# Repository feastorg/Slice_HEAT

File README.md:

# DC heating Element Controller Slice

DC heating Element Controller Slice for BREAD.

## Introduction

Two-channel controller for resistive DC heating elements, with a
MAX31855K thermocouple input per channel. Each channel has a high-side
P-channel MOSFET (AOD4185) that is on only while the bus E-stop and the
Nano's enable are both high, and a low-side N-channel MOSFET (AOD4184A)
switched by the Nano's PWM. A B340A freewheel diode sits across each
output.

## Ratings

- Heater supply: 12 V only, on its own terminal block J6 (VHTR+ and
  VHTR- = PGND), not from the bus. Fit an external 8 A slow-blow fuse
  in the + lead.
- Up to 3.5 A per channel, 7 A for both together.
- Resistive heaters: up to 3.5 A per channel. An inductive load (solenoid,
  fan, pump) relies on the on-board freewheel diodes D3/D4 alone, and they
  are B340A parts rated 3 A average: keep inductive loads to 3 A per
  channel.
- PGND meets the logic ground at one point on the board (NT1).
- FET heat: the drain tabs of Q2-Q4 sit on 1.74-1.93 cm2 of 1 oz
  copper each (F.Cu and B.Cu, joined by thermal vias; Q1 4.95 cm2), less
  than the 1 in2 of 2 oz behind the datasheets' RθJA. At 3.5 A and
  100 % duty, with RDS(on) at TJ 125 C, the AOD4184A low side dissipates
  0.20 W and the AOD4185 high side 0.38 W, so TJ at 50 C ambient is at
  most about 70 C and 88 C. These are estimates: RθJA is assumed to be
  100 C/W, not measured. Bench check before relying on 3.5 A: run
  both channels at 3.5 A for 30 minutes with a thermocouple on each FET
  tab (Q1-Q4).

## Connections

Wires enter all four terminal blocks from the right-hand board edge;
each position is marked on the silkscreen.

| Terminal | Pin | Signal | Use |
|---|---|---|---|
| J4 | 2 / 1 | HTR1+ / HTR1- | heater 1 |
| J5 | 2 / 1 | HTR2+ / HTR2- | heater 2 |
| J6 | 2 / 1 | VHTR+ / VHTR- (PGND) | 12 V heater supply in |
| J3 | 5 / 6 | TC1+ / TC1- | type K thermocouple, channel 1 (U2) |
| J3 | 7 / 8 | TC2+ / TC2- | type K thermocouple, channel 2 (U3) |
| J3 | 1 / 2, 3 / 4 | TMSTR1 (TH1) / GND, TMSTR2 (TH2) / GND | thermistor inputs (R1/R2 pull-ups to +5V) |

J4-J6 are Phoenix Contact SPT 2,5/ 2-H-5,0 (1990973): 2-position
push-in, 5 mm pitch, 24 A, 0.2-4 mm2 rigid or 0.2-2.5 mm2 flexible
wire, 10 mm strip length. J3 is a Phoenix Contact PT 1,5/ 8-3,5-H
(8-position push-in, 3.5 mm pitch).

E-stop: the bus E_STOP line (J2.6) must be high for the heaters to run.
Unwired, a 1 M pull-down holds it low and the heaters stay off.
JP1 (BENCH, open by default) pulls the line high through R18 (10 k) for use off
the loaf; leave it open in a loaf.

## Warnings

- Thermocouples: use insulated (sheathed or ungrounded-junction) probes.
  A junction touching a live heater conductor puts up to 12 V on T+/T-,
  far past the MAX31855's absolute maximum of VCC + 0.3 V (3.6 V on its
  3.3 V supply), and can destroy it.
- Heater supply polarity: J6 pin 2 is + (VHTR+), pin 1 is - (VHTR-).
  Reversed, the TVS D2 and
  the MOSFET body diodes with the freewheel diodes conduct straight
  across the supply until the external fuse opens, and C7 (polarised)
  is reverse biased. There is no reverse-polarity protection on the
  board: check the polarity before connecting the supply.

## Pin map (Arduino Nano, A1)

| Nano pin | Signal | Function |
|---|---|---|
| D11 | PWM1 | heater 1 low-side gate |
| D10 | PWM2 | heater 2 low-side gate |
| D12 | HTR_EN | high = high-side switches may turn on |
| D2 | ESTOP_SNS | buffered E-stop, input (high = run) |
| D9 | CLK | MAX31855 clock (software SPI, 3.3 V shifted) |
| D7 | DATA | MAX31855 SO |
| D8 | SS1 | thermocouple 1 chip select |
| D6 | SS2 | thermocouple 2 chip select |
| D5 | LED | WS2812B status LED |
| A0 / A1 | TMSTR1 / TMSTR2 | thermistor inputs (unused by the sketch) |
| A4 / A5 | I2C | bus I2C (slice address 6) |

## Usage

> **Draft firmware.** `firmware/HEAT.ino` is a minimal first sketch: it
> compiles but has not run on hardware, and it needs review and revision.
> Still to come: per-channel I2C reads (a read now returns channel 1
> only, and an I2C write sets both channels), a command watchdog, and the
> port to bread-slice-core.

Build `firmware/HEAT.ino` for an Arduino Nano (`arduino:avr:nano`). Over
serial at 115200 baud send `<ch>,<target C>,<ramp C/min>` (ch 1, 2 or 0
for both; ramp 0 steps straight to the target). The sketch prints
setpoint, temperature and duty for both channels once a second. It drops
HTR_EN and both PWMs on a thermocouple fault or above 100 C; that fault
holds until the next command.

The E-stop latches. E_STOP low (polled every 250 ms, and caught between
polls by a falling edge on D2/INT0) turns both heaters off and sets both
targets to 0, and the sketch ignores commands while latched. Releasing
the E-stop does not restart anything: clear the latch with `C` on serial
or the single byte 0x43 over I2C (it clears only with E_STOP high), or
reset the Nano, then send a new target. The hardware cut through the
high-side P-FETs works without the sketch.

## Documentation

Please refer to the [docs](/docs) for more info.

---

<div align="center">
  
</div>

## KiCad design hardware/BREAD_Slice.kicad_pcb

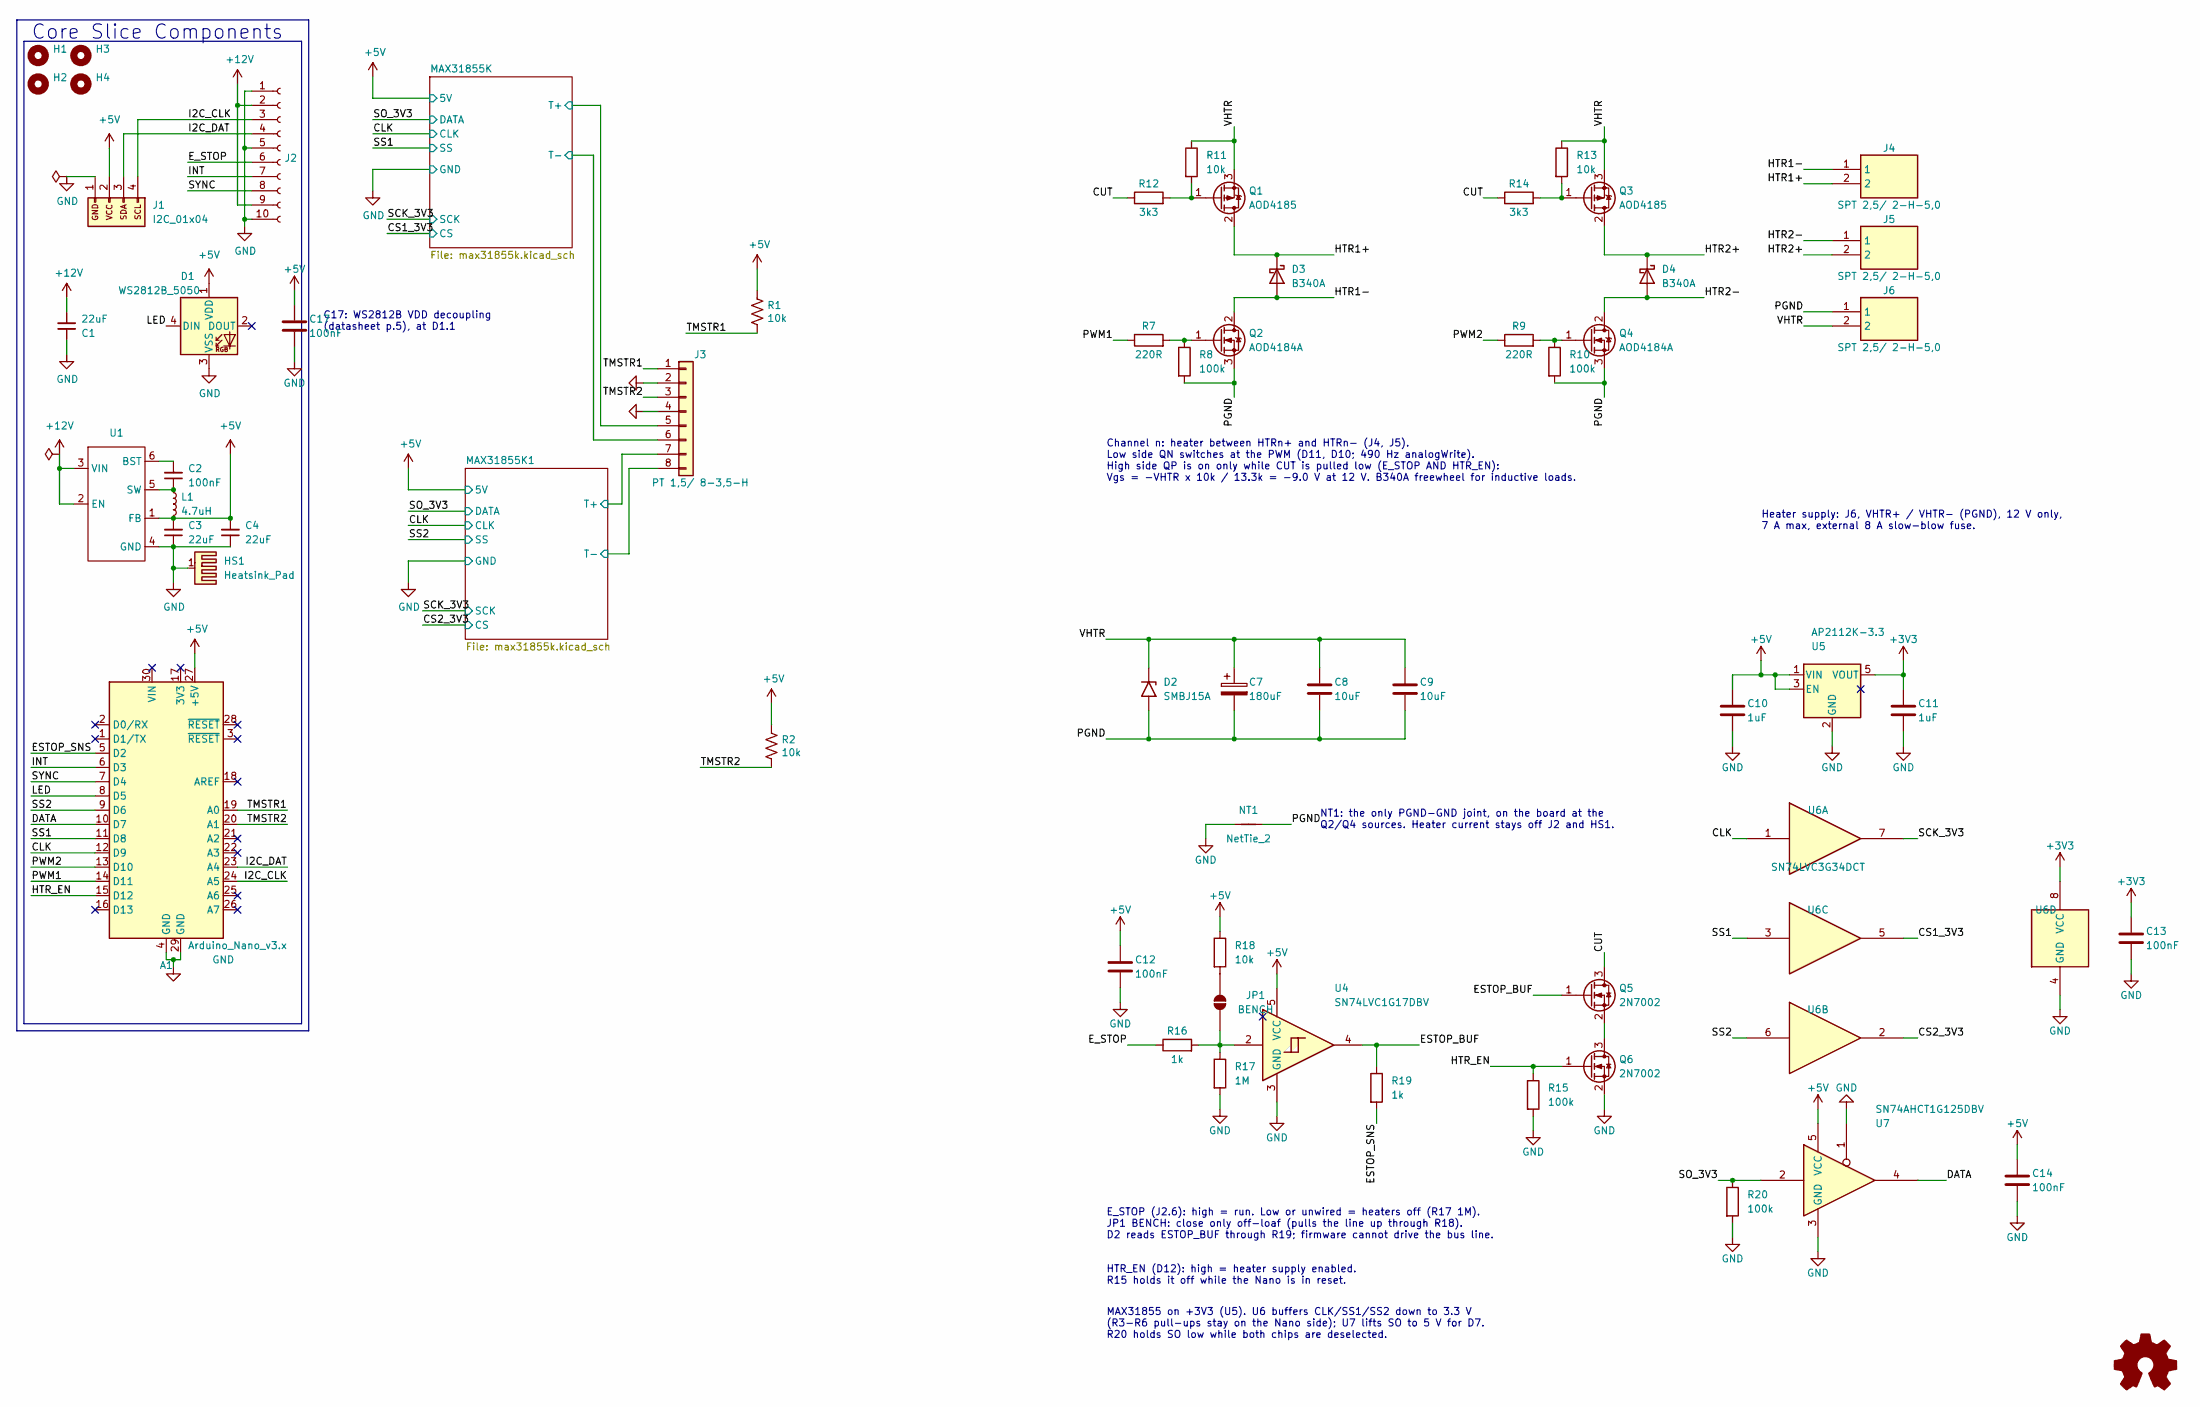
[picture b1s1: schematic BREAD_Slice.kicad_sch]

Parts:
A1: Arduino_Nano_v3.x; Arduino_Nano
C1, C3, C4: 22uF; C_1206_3216Metric
C2: 100nF; C_1206_3216Metric
C7: 180uF; CP_Radial_D8.0mm_P3.50mm; MPN RNU1E181MDN1
C8, C9: 10uF; C_1206_3216Metric; MPN GRM31CR71E106KA12L
C10, C11: 1uF; C_0805_2012Metric; MPN GRM21BR71E105KA99L
C12, C13, C14, C17: 100nF; C_0805_2012Metric; MPN CL21B104KBCNNNC
D1: WS2812B_5050; WS2812-5050-4PIN
D2: SMBJ15A; D_SMB; MPN SMBJ15A
D3, D4: B340A; D_SMA; MPN B340A-13-F
H1, H2, H3, H4: MountingHole; MountingHole_5mm
HS1: Heatsink_Pad; Thermal_Pad
J1: I2C_01x04; JST_SH_SM04B-SRSS-TB_1x04-1MP_P1.00mm_Horizontal
J2: Conn_01x10_Female; PinSocket_1x10_P2.54mm_Horizontal
J3: PT 1,5/ 8-3,5-H; TerminalBlock_Phoenix_PT-1,5-8-3.5-H_1x08_P3.50mm_Horizontal; Manufacturer_Part_Number 1984675
J4, J5, J6: SPT 2,5/ 2-H-5,0; 1990973; Manufacturer_Part_Number 1990973
JP1: BENCH; SolderJumper-2_P1.3mm_Open_RoundedPad1.0x1.5mm
L1: 4.7uH; L_1210_3225Metric
NT1: NetTie_2; NetTie-2_SMD_Pad2.0mm
Q1, Q3: AOD4185; TO-252-2; MPN AOD4185
Q2, Q4: AOD4184A; TO-252-2; MPN AOD4184A
Q5, Q6: 2N7002; SOT-23; MPN 2N7002-7-F
R1, R2: 10k; R_1206_3216Metric_Pad1.30x1.75mm_HandSolder
R7, R9: 220R; R_0805_2012Metric; MPN RC0805FR-07220RL
R8, R10, R15, R20: 100k; R_0805_2012Metric; MPN RC0805FR-07100KL
R11, R13, R18: 10k; R_0805_2012Metric; MPN RC0805FR-0710KL
R12, R14: 3k3; R_0805_2012Metric; MPN RC0805FR-073K3L
R16, R19: 1k; R_0805_2012Metric; MPN RC0805FR-071KL
R17: 1M; R_0805_2012Metric; MPN RC0805FR-071ML
U1: TSOT-23-6
U4: SN74LVC1G17DBV; SOT-23-5; MPN SN74LVC1G17DBVR
U5: AP2112K-3.3; SOT-23-5; MPN AP2112K-3.3TRG1
U6: SN74LVC3G34DCT; SSOP-8_2.95x2.8mm_P0.65mm; MPN SN74LVC3G34DCTR
U7: SN74AHCT1G125DBV; SOT-23-5; MPN SN74AHCT1G125DBVR

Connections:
+3V3: C11.1, C13.1, U5.5 (VOUT), U6.8 (VCC); also elsewhere on the board
+5V: A1.27 (+5V), C3.2, C4.2, C10.1, C12.1, C14.1, C17.1, D1.1 (VDD), J1.2, L1.2, R1.1, R2.1, R18.1, U1.1 (FB), U4.5 (VCC), U5.1 (VIN), U5.3 (EN), U7.5 (VCC); also elsewhere on the board
+12V: C1.2, J2.2, J2.9, U1.2 (EN), U1.3 (VIN)
/CLK: A1.12 (D9), U6.1; also elsewhere on the board
/CS1_3V3: U6.5; also elsewhere on the board
/CS2_3V3: U6.2; also elsewhere on the board
/CUT: Q5.3 (D), R12.1, R14.1
/DATA: A1.10 (D7), U7.4
/ESTOP_BUF: Q5.1 (G), R19.1, U4.4
/ESTOP_SNS: A1.5 (D2), R19.2
/E_STOP: J2.6, R16.1
/HTR1+: D3.1 (K), J4.2, Q1.2 (D)
/HTR1-: D3.2 (A), J4.1, Q2.2 (D)
/HTR2+: D4.1 (K), J5.2, Q3.2 (D)
/HTR2-: D4.2 (A), J5.1, Q4.2 (D)
/HTR_EN: A1.15 (D12), Q6.1 (G), R15.1
/I2C_CLK: A1.24 (A5), J1.4, J2.3
/I2C_DAT: A1.23 (A4), J1.3, J2.4
/INT: A1.6 (D3), J2.7
/LED: A1.8 (D5), D1.4 (DIN)
/MAX31855K1/T+: J3.7; also elsewhere on the board
/MAX31855K1/T-: J3.8; also elsewhere on the board
/MAX31855K/T+: J3.5; also elsewhere on the board
/MAX31855K/T-: J3.6; also elsewhere on the board
/PGND: C7.2, C8.2, C9.2, D2.2 (A2), J6.1, NT1.2, Q2.3 (S), Q4.3 (S), R8.2, R10.2
/PWM1: A1.14 (D11), R7.1
/PWM2: A1.13 (D10), R9.1
/SCK_3V3: U6.7; also elsewhere on the board
/SO_3V3: R20.1, U7.2; also elsewhere on the board
/SS1: A1.11 (D8), U6.3; also elsewhere on the board
/SS2: A1.9 (D6), U6.6; also elsewhere on the board
/SYNC: A1.7 (D4), J2.8
/TMSTR1: A1.19 (A0), J3.1, R1.2
/TMSTR2: A1.20 (A1), J3.3, R2.2
/VHTR: C7.1, C8.1, C9.1, D2.1 (A1), J6.2, Q1.3 (S), Q3.3 (S), R11.1, R13.1
GND: A1.4 (GND), A1.29 (GND), C1.1, C3.1, C4.1, C10.2, C11.2, C12.2, C13.2, C14.2, C17.2, D1.3 (VSS), HS1.1, J1.1, J2.1, J2.5, J2.10, J3.2, J3.4, NT1.1, Q6.2 (S), R15.2, R17.2, R20.2, U1.4 (GND), U4.3 (GND), U5.2 (GND), U6.4 (GND), U7.1, U7.3 (GND); also elsewhere on the board
unnamed: JP1.1 (A), R16.2, R17.1, U4.2
unnamed: JP1.2 (B), R18.2
unnamed: Q1.1 (G), R11.2, R12.2
unnamed: Q2.1 (G), R7.2, R8.1
unnamed: Q3.1 (G), R13.2, R14.2
unnamed: Q4.1 (G), R9.2, R10.1
unnamed: Q5.2 (S), Q6.3 (D)
unnamed: C2.2, U1.6 (BST)
unnamed: C2.1, L1.1, U1.5 (SW)

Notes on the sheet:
Core Slice Components
Channel n: heater between HTRn+ and HTRn- (J4, J5). Low side QN switches at the PWM (D11, D10; 490 Hz analogWrite). High side QP is on only while CUT is pulled low (E_STOP AND HTR_EN): Vgs = -VHTR x 10k / 13.3k = -9.0 V at 12 V. B340A freewheel for inductive loads.
Heater supply: J6, VHTR+ / VHTR- (PGND), 12 V only, 7 A max, external 8 A slow-blow fuse.
NT1: the only PGND-GND joint, on the board at the Q2/Q4 sources. Heater current stays off J2 and HS1.
E_STOP (J2.6): high = run. Low or unwired = heaters off (R17 1M). JP1 BENCH: close only off-loaf (pulls the line up through R18). D2 reads ESTOP_BUF through R19; firmware cannot drive the bus line.
HTR_EN (D12): high = heater supply enabled. R15 holds it off while the Nano is in reset.
MAX31855 on +3V3 (U5). U6 buffers CLK/SS1/SS2 down to 3.3 V (R3-R6 pull-ups stay on the Nano side); U7 lifts SO to 5 V for D7. R20 holds SO low while both chips are deselected.
C17: WS2812B VDD decoupling (datasheet p.5), at D1.1

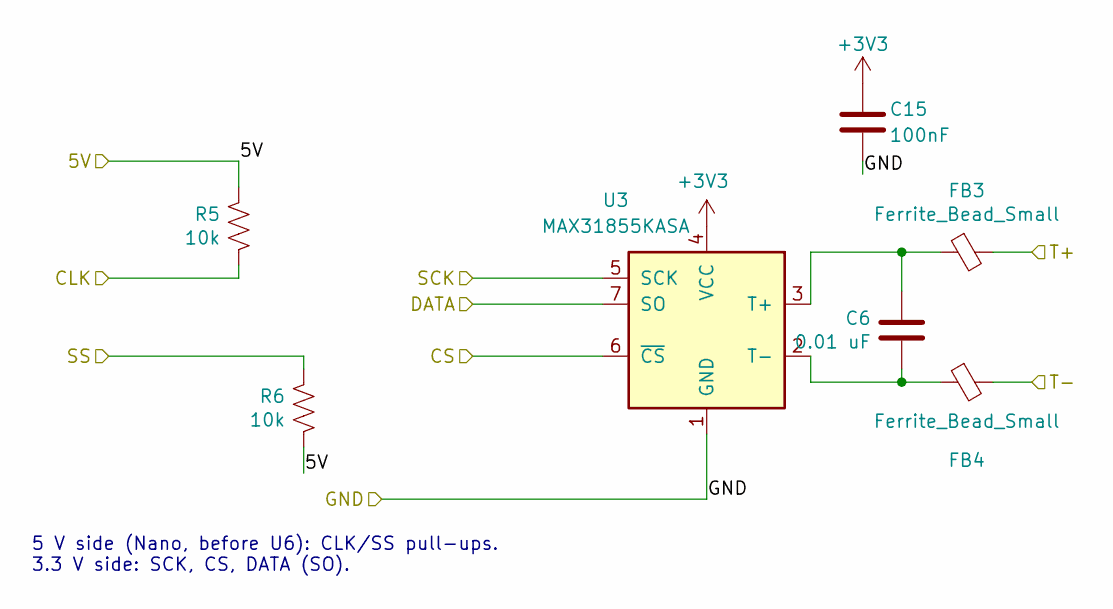
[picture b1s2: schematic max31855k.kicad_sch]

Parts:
C6: 0.01 uF; C_1206_3216Metric_Pad1.33x1.80mm_HandSolder
C15: 100nF; C_0805_2012Metric; MPN CL21B104KBCNNNC
FB3, FB4: Ferrite_Bead_Small; R_1206_3216Metric_Pad1.30x1.75mm_HandSolder
R5, R6: 10k; R_1206_3216Metric_Pad1.30x1.75mm_HandSolder
U3: MAX31855KASA; SOIC-8_3.9x4.9mm_P1.27mm

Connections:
+3V3: C15.1, U3.4 (VCC); also elsewhere on the board
+5V: R5.1, R6.2; also elsewhere on the board
/CLK: R5.2; also elsewhere on the board
/CS2_3V3: U3.6 (~CS); also elsewhere on the board
/MAX31855K1/T+: FB3.2; also elsewhere on the board
/MAX31855K1/T-: FB4.2; also elsewhere on the board
/SCK_3V3: U3.5 (SCK); also elsewhere on the board
/SO_3V3: U3.7 (SO); also elsewhere on the board
/SS2: R6.1; also elsewhere on the board
GND: C15.2, U3.1 (GND); also elsewhere on the board
unnamed: C6.1, FB3.1, U3.3 (T+)
unnamed: C6.2, FB4.1, U3.2 (T-)

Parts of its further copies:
C5: 0.01 uF; C_1206_3216Metric_Pad1.33x1.80mm_HandSolder
C16: 100nF; C_0805_2012Metric; MPN CL21B104KBCNNNC
FB1, FB2: Ferrite_Bead_Small; R_1206_3216Metric_Pad1.30x1.75mm_HandSolder
R3, R4: 10k; R_1206_3216Metric_Pad1.30x1.75mm_HandSolder
U2: MAX31855KASA; SOIC-8_3.9x4.9mm_P1.27mm

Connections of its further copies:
+3V3: C16.1, U2.4 (VCC); also elsewhere on the board
+5V: R3.1, R4.2; also elsewhere on the board
/CLK: R3.2; also elsewhere on the board
/CS1_3V3: U2.6 (~CS); also elsewhere on the board
/MAX31855K/T+: FB1.2; also elsewhere on the board
/MAX31855K/T-: FB2.2; also elsewhere on the board
/SCK_3V3: U2.5 (SCK); also elsewhere on the board
/SO_3V3: U2.7 (SO); also elsewhere on the board
/SS1: R4.1; also elsewhere on the board
GND: C16.2, U2.1 (GND); also elsewhere on the board
unnamed: C5.1, FB1.1, U2.3 (T+)
unnamed: C5.2, FB2.1, U2.2 (T-)

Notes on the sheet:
5 V side (Nano, before U6): CLK/SS pull-ups. 3.3 V side: SCK, CS, DATA (SO).

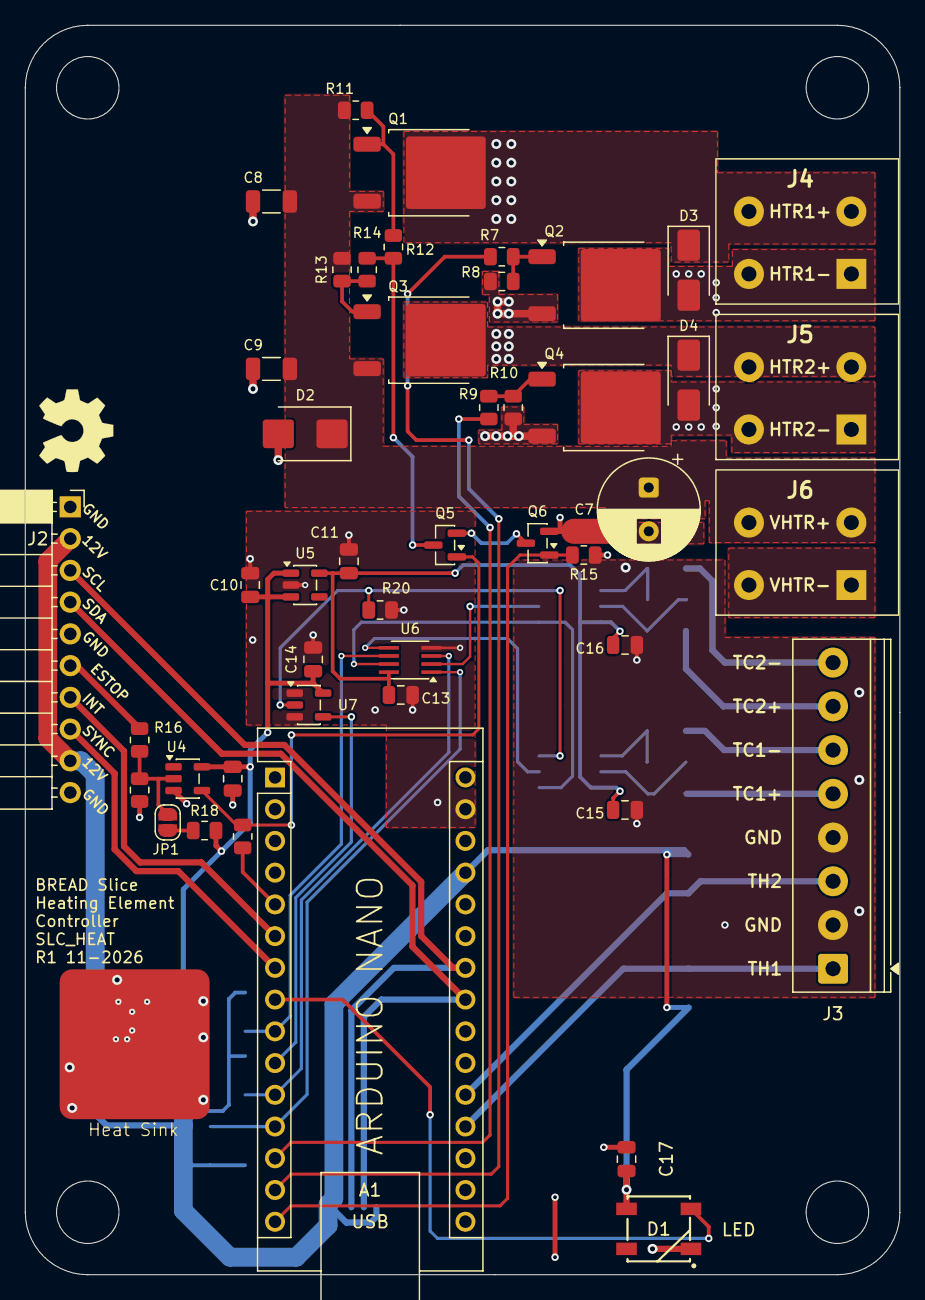
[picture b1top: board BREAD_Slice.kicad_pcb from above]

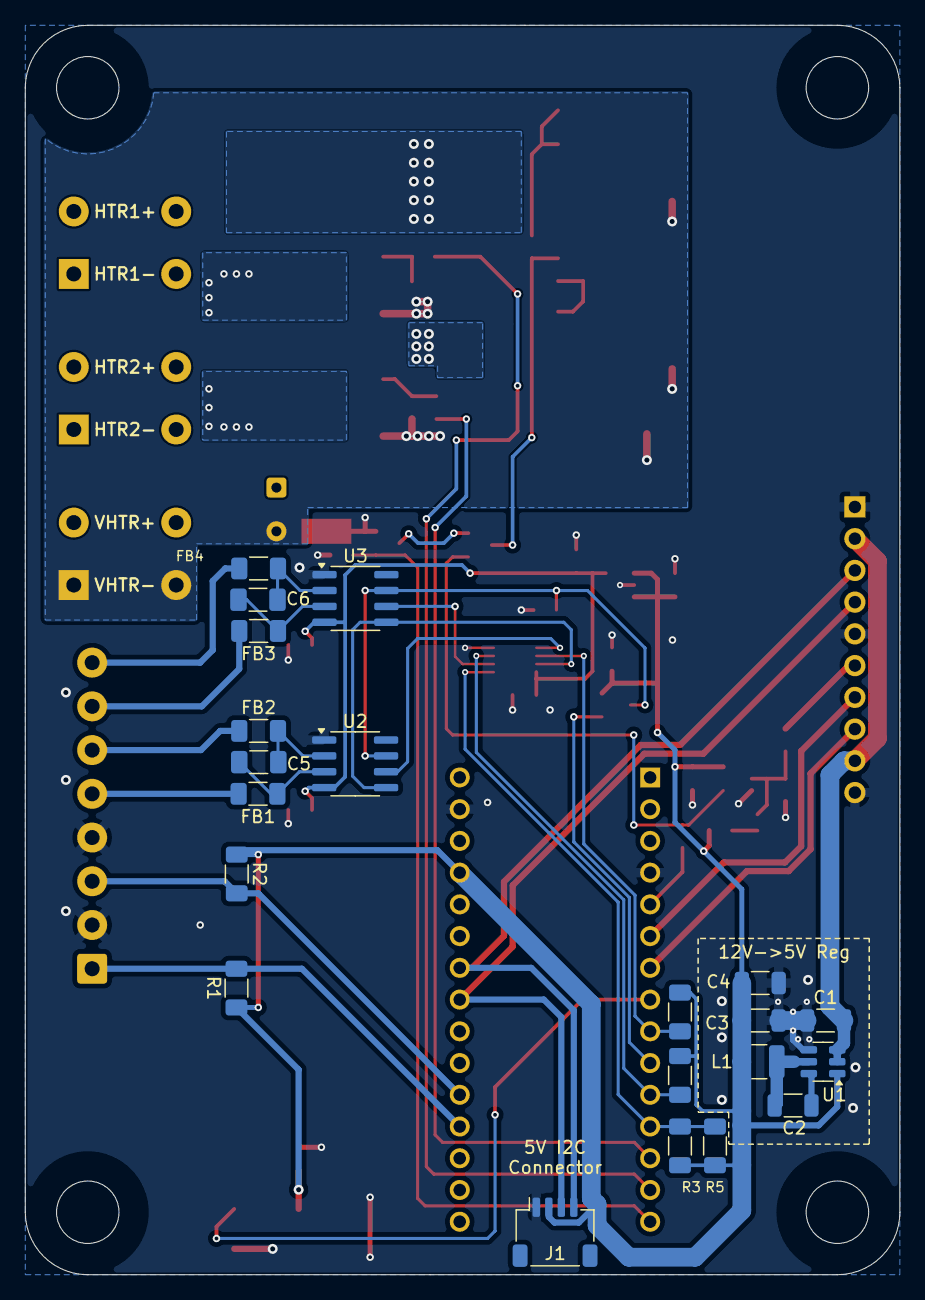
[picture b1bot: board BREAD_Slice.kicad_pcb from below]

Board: 2 copper layers, 70.0 x 100.0 mm, 74 parts (21 on the bottom side), 49 nets.

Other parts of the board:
Logo1: Logo_Open_Hardware_Small; OSHW-Symbol_6.7x6mm_SilkScreen

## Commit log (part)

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2024-09-10 set repo
2024-09-10 upgraded by duplicating ciruit, new core, all back copper
2024-09-10 firmware files fix
2024-09-10 removed old design
2024-09-12 minor fixes
2024-09-12 updated to the correct terminals and proper hierarchial pages
2024-09-30 JLCPCB order rev-A
2026-04-18 chore: minor updates
2026-04-18 chore: update to kicad9
2026-04-18 chore: add error sev.
2026-05-20 Add slice.yaml manifest (schema v1.0)
2026-05-24 Add KiBot/docs pipeline
2026-05-24 Update TODO with CI findings (ERC errors)
